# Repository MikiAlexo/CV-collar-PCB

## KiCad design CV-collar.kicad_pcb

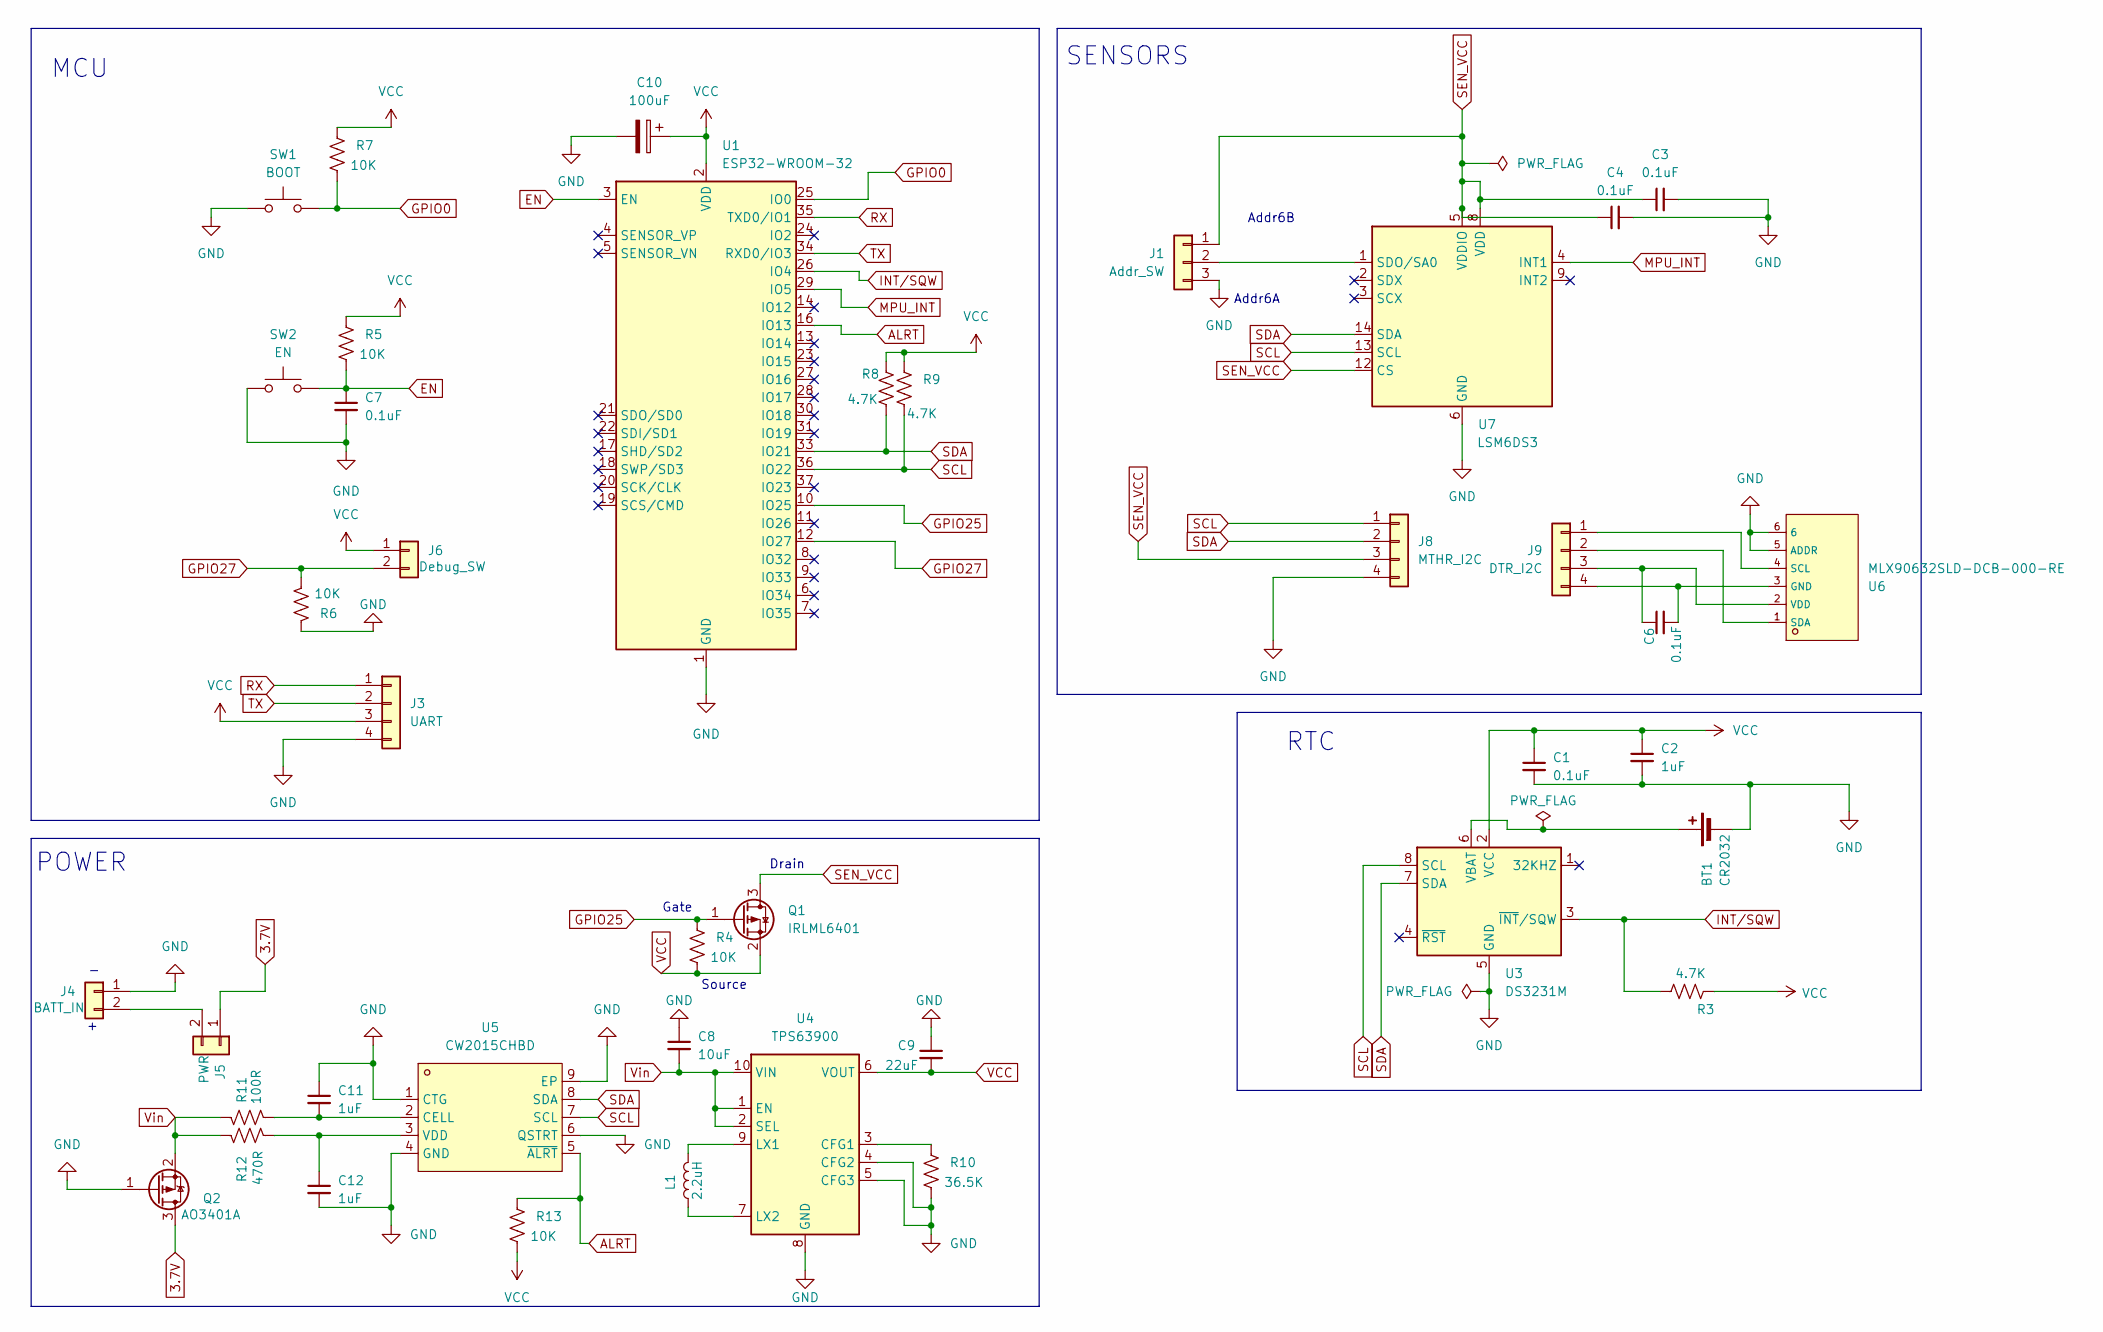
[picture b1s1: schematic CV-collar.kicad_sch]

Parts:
BT1: CR2032; BatteryHolder_Keystone_1060_1x2032; LCSC Part # C70377
C1, C3, C4, C6, C7: 0.1uF; C_0603_1608Metric; LCSC Part # C1525
C2, C11, C12: 1uF; C_0603_1608Metric; LCSC Part # C1848
C8: 10uF; C_0603_1608Metric; LCSC Part # C15525
C9: 22uF; C_1206_3216Metric; LCSC Part # C59461
C10: 100uF; CP_Elec_6.3x5.4; LCSC Part # C3338
J1: Addr_SW; PinHeader_1x03_P2.54mm_Vertical
J3: UART; PinHeader_1x04_P2.54mm_Vertical
J4: BATT_IN; PinHeader_1x02_P2.54mm_Vertical
J5: PWR; PinHeader_1x02_P2.54mm_Vertical
J6: Debug_SW; PinHeader_1x02_P2.54mm_Vertical
J8: MTHR_I2C; PinHeader_1x04_P2.54mm_Vertical
J9: DTR_I2C; PinHeader_1x04_P2.54mm_Vertical
L1: 2.2uH; L_1008_2520Metric; LCSC Part # C354563
Q1: IRLML6401; SOT-23; LCSC Part # C347501
Q2: AO3401A; SOT-23; LCSC Part # C15127
R3, R8, R9: 4.7K; R_0603_1608Metric; LCSC Part # C17673
R4, R5, R6, R7, R13: 10K; R_0603_1608Metric; LCSC Part # C17414
R10: 36.5K; R_0603_1608Metric; Tolerance 1%; LCSC Part # C23029
R11: 100R; R_0603_1608Metric; LCSC Part # C17408
R12: 470R; R_0603_1608Metric; LCSC Part # C17710
SW1: BOOT; SW_Push_1P1T_NO_CK_KSC6xxG; LCSC Part # C49023761
SW2: EN; SW_Push_1P1T_NO_CK_KSC6xxG; LCSC Part # C49023761
U1: ESP32-WROOM-32; LCSC Part # C701341
U3: DS3231M; SOIC-8_3.9x4.9mm_P1.27mm; LCSC Part # C107410
U4: TPS63900; WSON-10-1EP_2.5x2.5mm_P0.5mm_EP1.2x2mm_ThermalVias; LCSC Part # C1518762
U5: CW2015CHBD; TDFN-8_L3.0-W2.0-P0.50-BL-EP; MPN CW2015CHBD; LCSC Part C881838
U6: MLX90632SLD-DCB-000-RE; SENSOR-SMD_MLX90632; LCSC C7541116
U7: LSM6DS3; LGA-14_3x2.5mm_P0.5mm_LayoutBorder3x4y

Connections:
3.7V: J5.1, Q2.3 (D)
ALRT: R13.1, U1.16 (IO13), U5.5 (~ALRT)
EN: C7.1, R5.2, SW2.2, U1.3 (EN)
GPIO0: R7.2, SW1.2, U1.25 (IO0)
GPIO25: Q1.1 (G), R4.1, U1.10 (IO25)
GPIO27: J6.2, R6.2, U1.12 (IO27)
INT/SQW: R3.2, U1.26 (IO4), U3.3 (~INT/SQW)
MPU_INT: U1.29 (IO5), U7.4 (INT1)
unnamed: BT1.1 (+), U3.6 (VBAT)
unnamed: J1.2, U7.1 (SDO/SA0)
unnamed: J4.2, J5.2
unnamed: J9.1, U6.4 (SCL)
unnamed: J9.2, U6.1 (SDA)
unnamed: C6.1, J9.3, U6.2 (VDD)
unnamed: R10.1, U4.3 (CFG1)
unnamed: L1.2, U4.9 (LX1)
unnamed: L1.1, U4.7 (LX2)
unnamed: C11.2, R11.2, U5.2 (CELL)
unnamed: C12.1, R12.2, U5.3 (VDD)
RX: J3.1, U1.35 (TXD0/IO1)
SCL: J8.1, R9.2, U1.36 (IO22), U3.8 (SCL), U5.7 (SCL), U7.13 (SCL)
SDA: J8.2, R8.2, U1.33 (IO21), U3.7 (SDA), U5.8 (SDA), U7.14 (SDA)
SEN_VCC: C3.1, C4.1, J1.1, J8.3, Q1.3 (D), U7.5 (VDDIO), U7.8 (VDD), U7.12 (CS)
TX: J3.2, U1.34 (RXD0/IO3)
VCC: C1.1, C2.1, C9.2, C10.1, J3.3, J6.1, Q1.2 (S), R3.1, R4.2, R5.1, R7.1, R8.1, R9.1, R13.2, U1.2 (VDD), U3.2 (VCC), U4.6 (VOUT)
Vin: C8.2, Q2.2 (S), R11.1, R12.1, U4.1 (EN), U4.2 (SEL), U4.10 (VIN)

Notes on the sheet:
Drain
Addr6B
Source
POWER
MCU
Gate
SENSORS
RTC
Addr6A

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
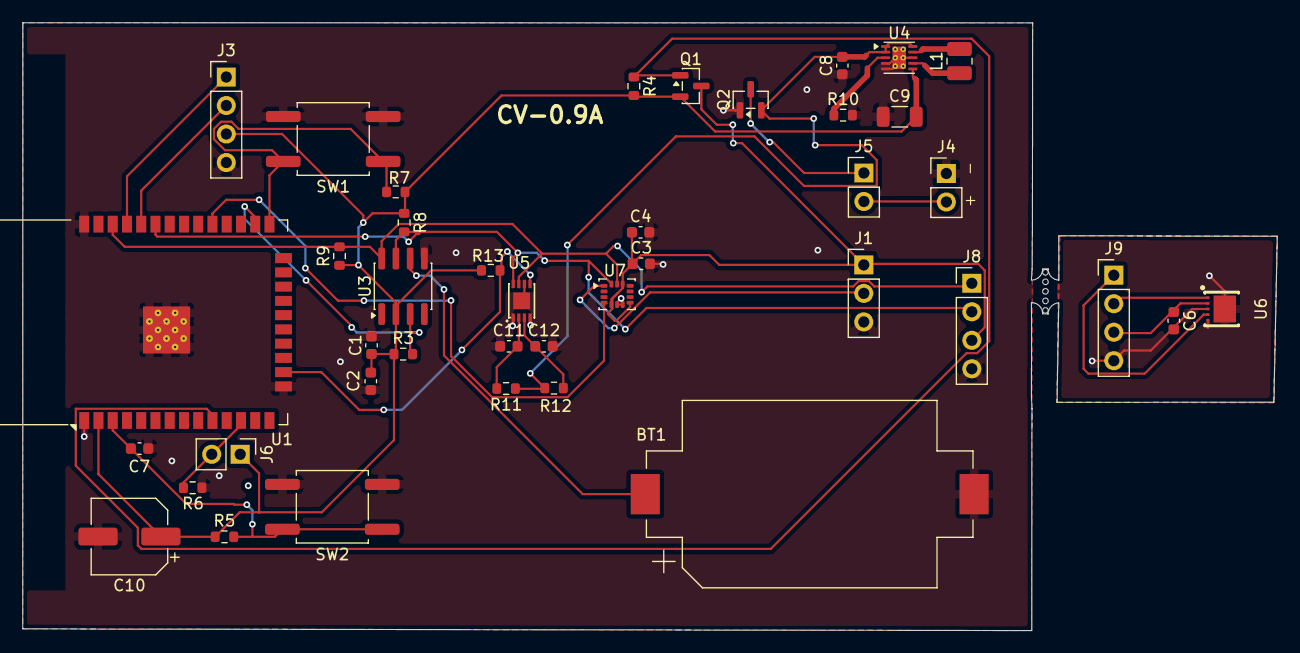
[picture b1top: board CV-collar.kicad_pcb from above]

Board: 2 copper layers, 111.8 x 54.2 mm, 41 parts (0 on the bottom side), 27 nets.

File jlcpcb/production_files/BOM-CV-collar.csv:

Comment,Designator,Footprint,LCSC,Quantity
0.1uF,"C1,C3,C4,C6,C7",C_0603_1608Metric,C1525,5
100R,R11,R_0603_1608Metric,C17408,1
100uF,C10,CP_Elec_6.3x5.4,C3338,1
10K,"R13,R4,R5,R6,R7",R_0603_1608Metric,C17414,5
10uF,C8,C_0603_1608Metric,C15525,1
1uF,"C11,C12,C2",C_0603_1608Metric,C1848,3
2.2uH,L1,L_1008_2520Metric,C354563,1
22uF,C9,C_1206_3216Metric,C59461,1
36.5K,R10,R_0603_1608Metric,C23029,1
4.7K,"R3,R8,R9",R_0603_1608Metric,C17673,3
470R,R12,R_0603_1608Metric,C17710,1
AO3401A,Q2,SOT-23,C15127,1
BATT_IN,J4,PinHeader_1x02_P2.54mm_Vertical,C5375081,1
BOOT,SW1,SW_Push_1P1T_NO_CK_KSC6xxG,C49023761,1
CW2015CHBD,U5,TDFN-8_L3.0-W2.0-P0.50-BL-EP,C881838,1
DS3231M,U3,SOIC-8_3.9x4.9mm_P1.27mm,C107410,1
DTR_I2C,J9,PinHeader_1x04_P2.54mm_Vertical,C5375081,1
Debug_SW,J6,PinHeader_1x02_P2.54mm_Vertical,C5375081,1
EN,SW2,SW_Push_1P1T_NO_CK_KSC6xxG,C49023761,1
ESP32-WROOM-32,U1,ESP32-WROOM-32,C701341,1
IRLML6401,Q1,SOT-23,C347501,1
MLX90632SLD-DCB-000-RE,U6,SENSOR-SMD_MLX90632,C7541116,1
MTHR_I2C,J8,PinHeader_1x04_P2.54mm_Vertical,C5375081,1
PWR,J5,PinHeader_1x02_P2.54mm_Vertical,C5375081,1
TPS63900,U4,WSON-10-1EP_2.5x2.5mm_P0.5mm_EP1.2x2mm_ThermalVias,C1518762,1
UART,J3,PinHeader_1x04_P2.54mm_Vertical,C5375081,1
CR2032,BT1,BatteryHolder_Keystone_1060_1x2032,,1
LSM6DS3,U7,LGA-14_3x2.5mm_P0.5mm_LayoutBorder3x4y,,1
Addr_SW,J1,PinHeader_1x03_P2.54mm_Vertical,,1
